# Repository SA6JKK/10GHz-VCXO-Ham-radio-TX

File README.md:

# 10GHz-VCXO-Ham-radio-TX
 A 10 GHz VCXO based FSK transmitter for ham radio

Goal: 0dBm to antenna. 

Goal: Output frequency between 10367-10369 MHz.  

Goal 75x120 mm PCB that fits HAMMOND 1455J1201RD 

https://se.farnell.com/hammond/1455j1201rd/pcb-box-enclosure-alum-red/dp/2469294

VCXO control from external BNC connector. FSK-CW or FSK modes. 

Aisler four layer "HD PCB" stackup for somewhat close to 50 ohms with cheap FR4 substrate. 

# Project Status: 

Schematic: Finished 

Layout: Finished and ordered

Verification: Not fully working :(

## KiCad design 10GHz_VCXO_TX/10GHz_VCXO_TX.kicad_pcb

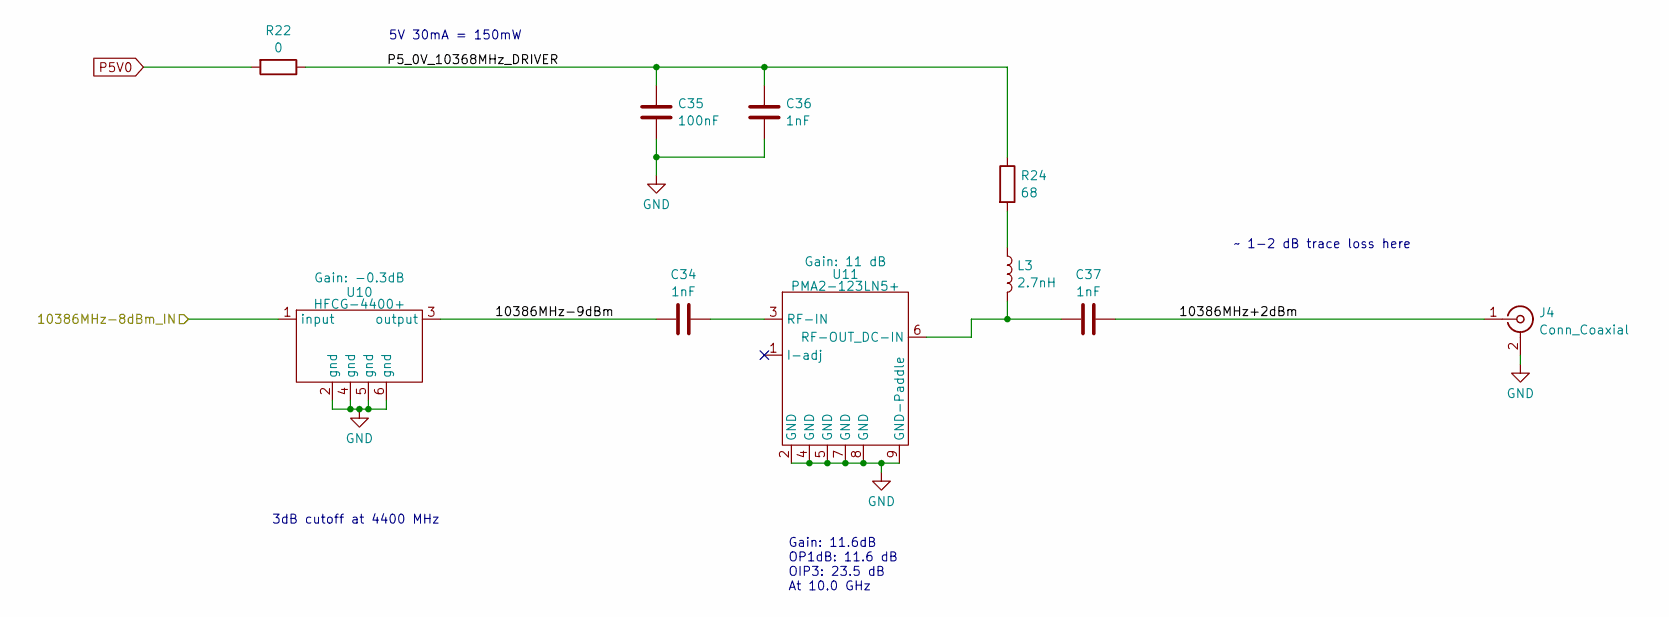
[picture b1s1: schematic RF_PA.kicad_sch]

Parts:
C34, C36, C37: 1nF; C_0402_1005Metric_Pad0.74x0.62mm_HandSolder
C35: 100nF; C_0603_1608Metric_Pad1.08x0.95mm_HandSolder
J4: Conn_Coaxial; SMA_Amphenol_901-143_Horizontal
L3: 2.7nH; L_0603_1608Metric_Pad1.05x0.95mm_HandSolder
R22: 0; R_0603_1608Metric_Pad0.98x0.95mm_HandSolder
R24: 68; R_2512_6332Metric_Pad1.40x3.35mm_HandSolder
U10: HFCG-4400+; Broadcom_DFN-6_2x2mm_P0.65mm
U11: PMA2-123LN5+; DFN-8-1EP_2x2mm_P0.5mm_EP0.6x1.2mm

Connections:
/3x_RF_Multiplier/10368MHz-8dBm_OUT: U10.1 (input); also elsewhere on the board
/RF_PA/10386MHz+2dBm: C37.1, J4.1 (In)
/RF_PA/10386MHz-9dBm: C34.1, U10.3 (output)
/RF_PA/P5_0V_10368MHz_DRIVER: C35.2, C36.2, R22.1, R24.1
GND: C35.1, C36.1, J4.2 (Ext), U10.2 (gnd), U10.4 (gnd), U10.5 (gnd), U10.6 (gnd), U11.2 (GND), U11.4 (GND), U11.5 (GND), U11.7 (GND), U11.8 (GND), U11.9 (GND-Paddle); also elsewhere on the board
unnamed: L3.1, R24.2
unnamed: C34.2, U11.3 (RF-IN)
unnamed: C37.2, L3.2, U11.6 (RF-OUT_DC-IN)
P5V0: R22.2; also elsewhere on the board

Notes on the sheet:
3dB cutoff at 4400 MHz
~ 1-2 dB trace loss here
5V 30mA = 150mW
Gain: 11.6dB OP1dB: 11.6 dB OIP3: 23.5 dB At 10.0 GHz

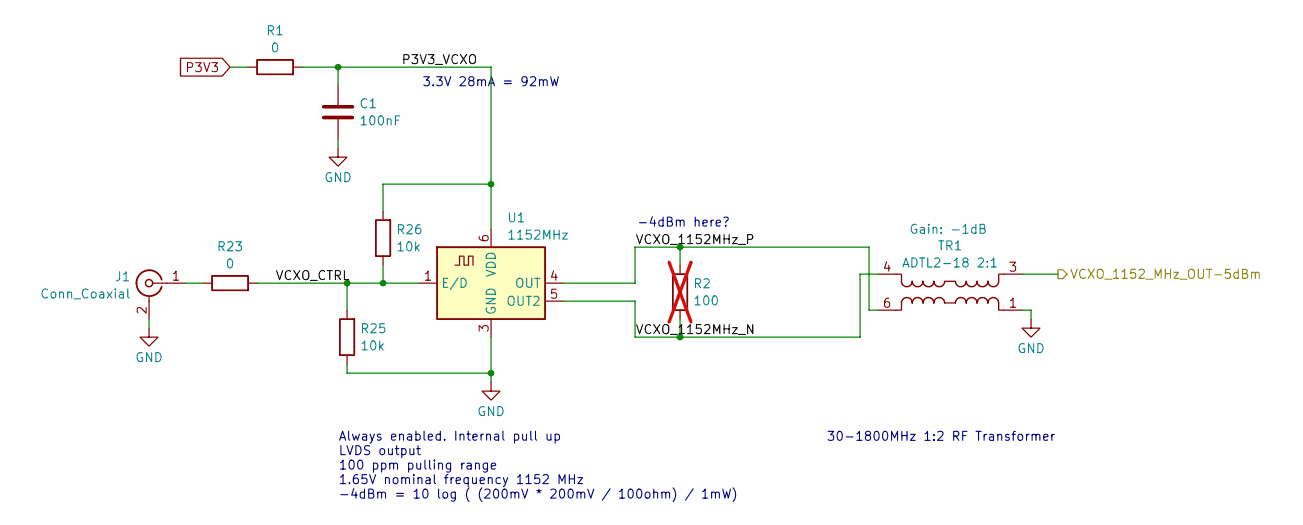
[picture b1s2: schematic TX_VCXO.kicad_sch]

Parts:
C1: 100nF; C_0603_1608Metric_Pad1.08x0.95mm_HandSolder
J1: Conn_Coaxial; BNC_Amphenol_B6252HB-NPP3G-50_Horizontal
R1, R23: 0; R_0603_1608Metric_Pad0.98x0.95mm_HandSolder
R2: 100; R_0603_1608Metric_Pad0.98x0.95mm_HandSolder; not fitted
R25, R26: 10k; R_0603_1608Metric_Pad0.98x0.95mm_HandSolder
TR1: ADTL2-18 2:1; Mini-Circuits_CD542_H2.84mm
U1: 1152MHz; Oscillator_SMD_IDT_JU6-6_7.0x5.0mm_P2.54mm

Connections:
/TX_VCXO/P3V3_VCXO: C1.1, R1.2, R26.2, U1.6 (VDD)
/TX_VCXO/VCXO_1152MHz_N: R2.2, TR1.4, U1.5 (OUT2)
/TX_VCXO/VCXO_1152MHz_P: R2.1, TR1.6, U1.4 (OUT)
/TX_VCXO/VCXO_1152_MHz_OUT-5dBm: TR1.3; also elsewhere on the board
/TX_VCXO/VCXO_CTRL: R23.2, R25.2, R26.1, U1.1 (E/D)
GND: C1.2, J1.2 (Ext), R25.1, TR1.1, U1.3 (GND); also elsewhere on the board
unnamed: J1.1 (In), R23.1
P3V3: R1.1; also elsewhere on the board

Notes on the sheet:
Always enabled. Internal pull up LVDS output 100 ppm pulling range 1.65V nominal frequency 1152 MHz -4dBm = 10 log ( (200mV * 200mV / 100ohm) / 1mW)
-4dBm here?
3.3V 28mA = 92mW
30-1800MHz 1:2 RF Transformer

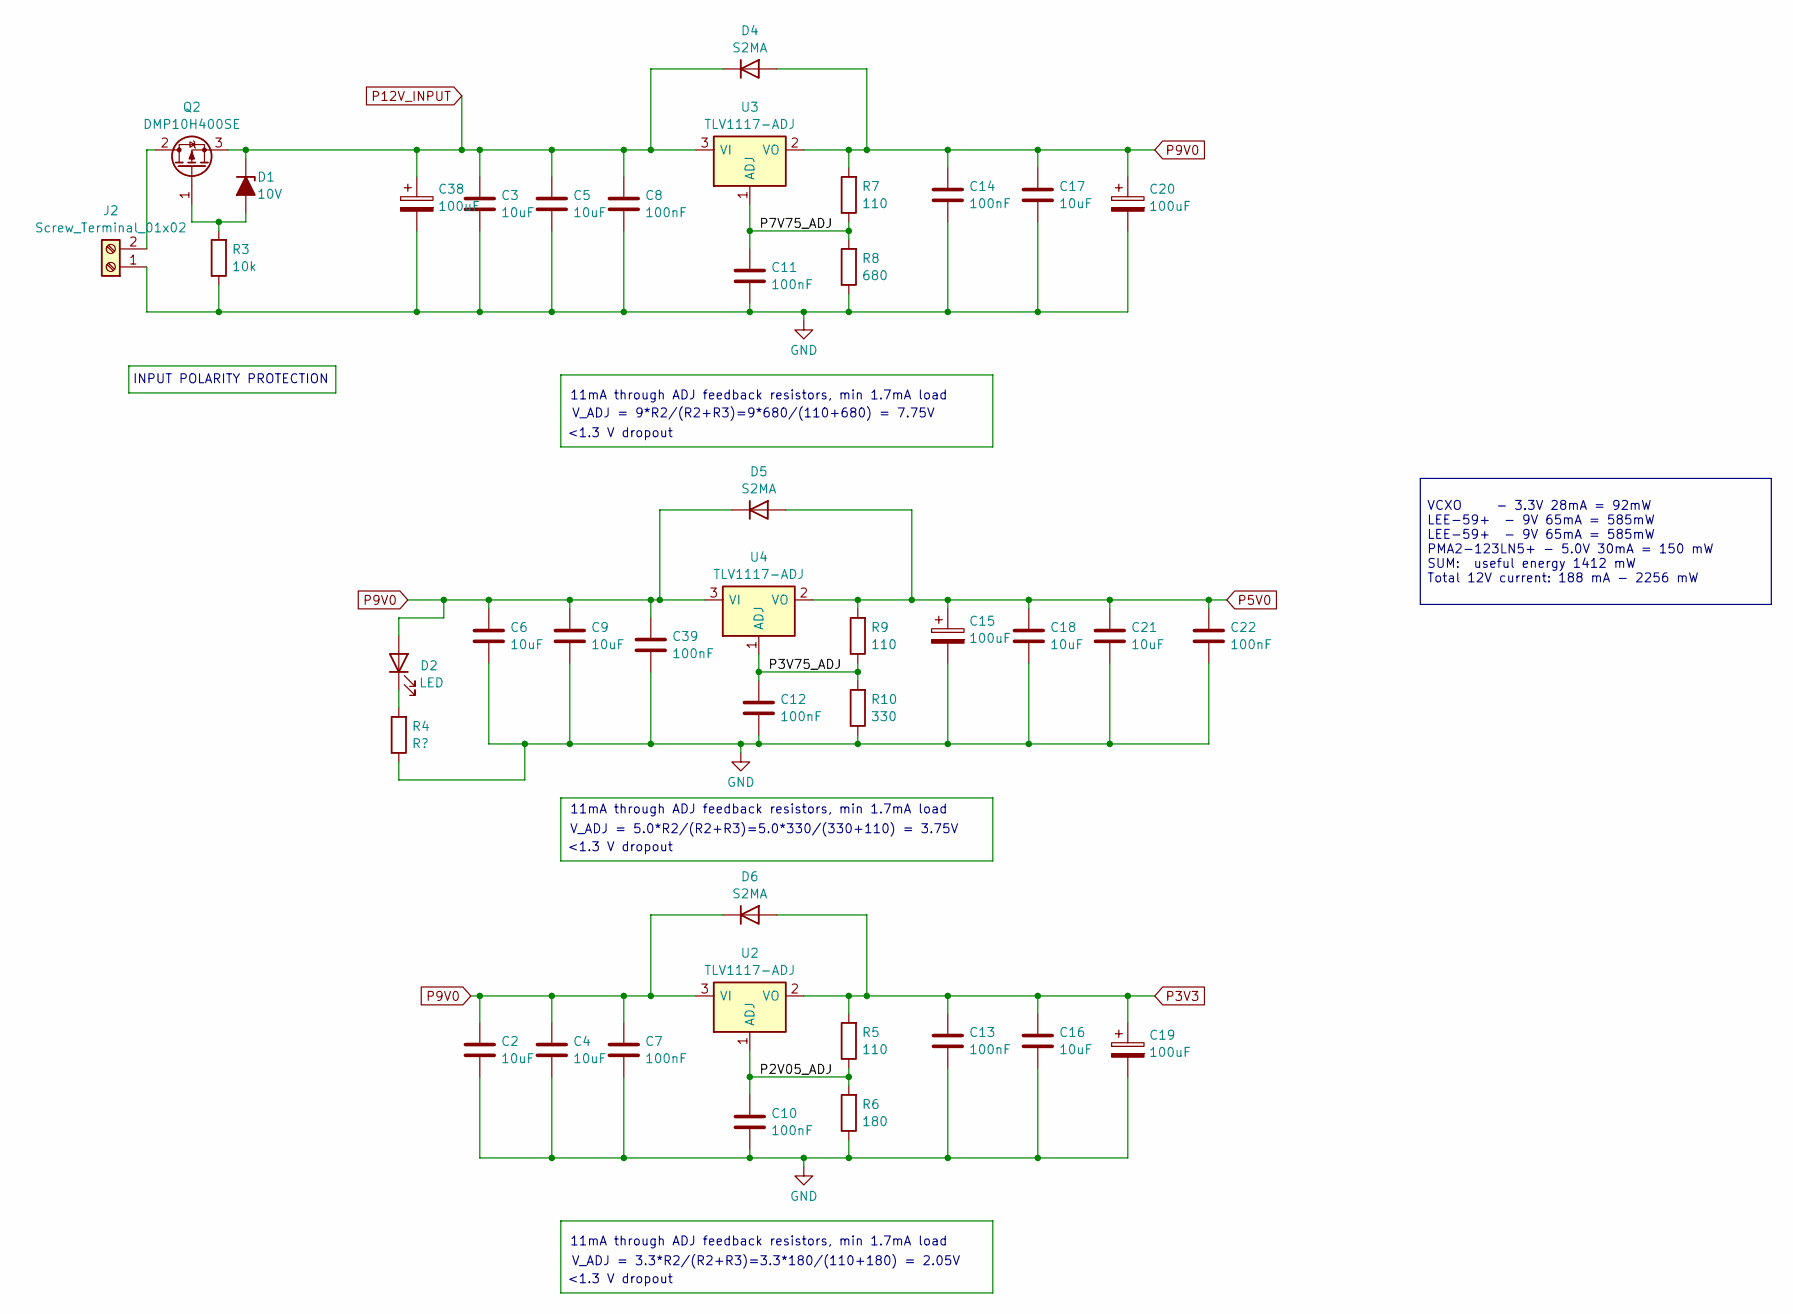
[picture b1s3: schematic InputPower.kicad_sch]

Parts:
C2, C3, C4, C5, C6, C9, C16, C17, C18, C21: 10uF; C_0805_2012Metric_Pad1.18x1.45mm_HandSolder
C7, C8, C10, C11, C12, C13, C14, C22, C39: 100nF; C_0603_1608Metric_Pad1.08x0.95mm_HandSolder
C15, C19, C20, C38: 100uF; CP_Elec_6.3x7.7
D1: 10V; D_SMA
D2: LED; LED_D3.0mm_Horizontal_O6.35mm_Z10.0mm
D4, D5, D6: S2MA; D_SMA
J2: Screw_Terminal_01x02; Altech_AK100_1x02_P5.00mm
Q2: DMP10H400SE; SOT-223-3_TabPin2
R3: 10k; R_0603_1608Metric_Pad0.98x0.95mm_HandSolder
R4: R?; R_0603_1608Metric_Pad0.98x0.95mm_HandSolder
R5, R7, R9: 110; R_0603_1608Metric_Pad0.98x0.95mm_HandSolder
R6: 180; R_0603_1608Metric_Pad0.98x0.95mm_HandSolder
R8: 680; R_0603_1608Metric_Pad0.98x0.95mm_HandSolder
R10: 330; R_0603_1608Metric_Pad0.98x0.95mm_HandSolder
U2, U3, U4: TLV1117-ADJ; SOT-223-3_TabPin2

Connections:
/InputPower/P2V05_ADJ: C10.2, R5.1, R6.2, U2.1 (ADJ)
/InputPower/P3V75_ADJ: C12.2, R9.1, R10.2, U4.1 (ADJ)
/InputPower/P7V75_ADJ: C11.2, R7.1, R8.2, U3.1 (ADJ)
GND: C2.1, C3.1, C4.1, C5.1, C6.1, C7.1, C8.1, C9.1, C10.1, C11.1, C12.1, C13.2, C14.1, C15.2, C16.2, C17.1, C18.1, C19.2, C20.2, C21.1, C22.1, C38.2, C39.1, J2.1, R3.1, R4.1, R6.1, R8.1, R10.1; also elsewhere on the board
unnamed: D1.2 (A), Q2.1 (G), R3.2
unnamed: D2.1 (K), R4.2
unnamed: J2.2, Q2.2 (D)
P3V3: C13.1, C16.1, C19.1, D6.2 (A), R5.2, U2.2 (VO); also elsewhere on the board
P5V0: C15.1, C18.2, C21.2, C22.2, D5.2 (A), R9.2, U4.2 (VO); also elsewhere on the board
P9V0: C2.2, C4.2, C6.2, C7.2, C9.2, C14.2, C17.2, C20.1, C39.2, D2.2 (A), D4.2 (A), D5.1 (K), D6.1 (K), R7.2, U2.3 (VI), U3.2 (VO), U4.3 (VI); also elsewhere on the board
P12V_INPUT: C3.2, C5.2, C8.2, C38.1, D1.1 (K), D4.1 (K), Q2.3 (S), U3.3 (VI)

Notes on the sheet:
<1.3 V dropout
11mA through ADJ feedback resistors, min 1.7mA load
V_ADJ = 9*R2/(R2+R3)=9*680/(110+680) = 7.75V
VCXO - 3.3V 28mA = 92mW LEE-59+ - 9V 65mA = 585mW LEE-59+ - 9V 65mA = 585mW PMA2-123LN5+ - 5.0V 30mA = 150 mW SUM: useful energy 1412 mW Total 12V current: 188 mA - 2256 mW
INPUT POLARITY PROTECTION
V_ADJ = 5.0*R2/(R2+R3)=5.0*330/(330+110) = 3.75V
V_ADJ = 3.3*R2/(R2+R3)=3.3*180/(110+180) = 2.05V

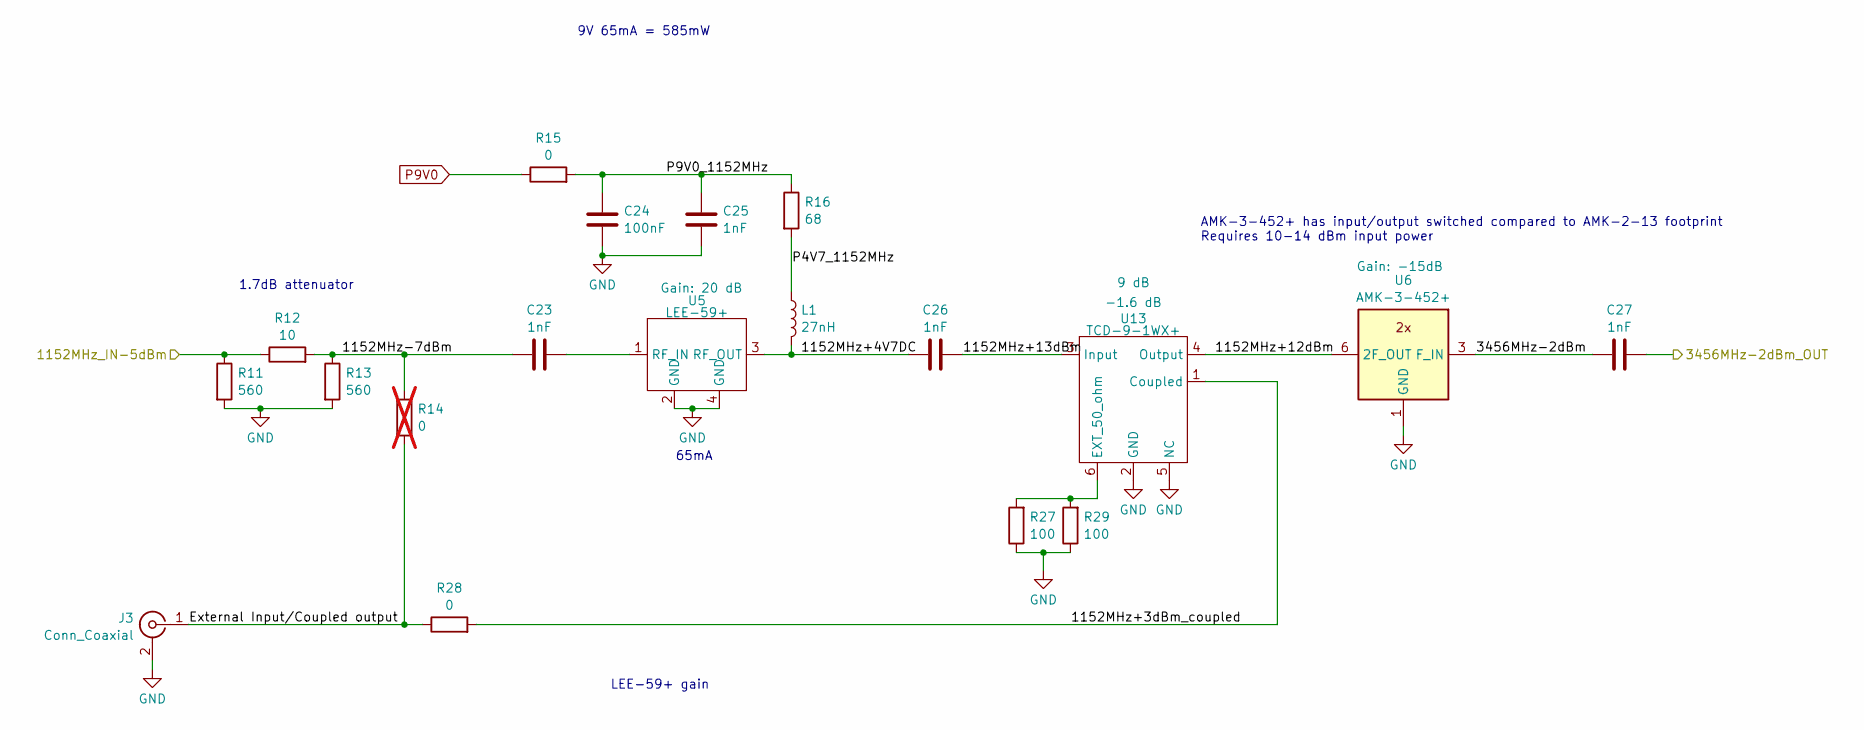
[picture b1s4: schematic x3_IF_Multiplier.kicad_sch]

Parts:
C23, C25, C26, C27: 1nF; C_0402_1005Metric_Pad0.74x0.62mm_HandSolder
C24: 100nF; C_0603_1608Metric_Pad1.08x0.95mm_HandSolder
J3: Conn_Coaxial; SMA_Amphenol_901-143_Horizontal
L1: 27nH; L_0603_1608Metric_Pad1.05x0.95mm_HandSolder
R11, R13: 560; R_0603_1608Metric_Pad0.98x0.95mm_HandSolder
R12: 10; R_0603_1608Metric_Pad0.98x0.95mm_HandSolder
R14: 0; R_0603_1608Metric_Pad0.98x0.95mm_HandSolder; not fitted
R15, R28: 0; R_0603_1608Metric_Pad0.98x0.95mm_HandSolder
R16: 68; R_2512_6332Metric_Pad1.40x3.35mm_HandSolder
R27, R29: 100; R_0603_1608Metric_Pad0.98x0.95mm_HandSolder
U5: LEE-59+; Mini-Circuits_FG873-4_3x3mm
U6: AMK-3-452+; Mini-Circuits_CD542_LandPatternPL-052
U13: TCD-9-1WX+; Mini-Circuits_DB1627

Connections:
/3x_RF_Multiplier/3456MHz-2dBm_IN: C27.2; also elsewhere on the board
/TX_VCXO/VCXO_1152_MHz_OUT-5dBm: R11.1, R12.1; also elsewhere on the board
/x3_IF_Multiplier/1152MHz+3dBm_coupled: R28.2, U13.1 (Coupled)
/x3_IF_Multiplier/1152MHz+4V7DC: C26.1, L1.2, U5.3 (RF_OUT)
/x3_IF_Multiplier/1152MHz+12dBm: U6.6 (2F_OUT), U13.4 (Output)
/x3_IF_Multiplier/1152MHz+13dBm: C26.2, U13.3 (Input)
/x3_IF_Multiplier/1152MHz-7dBm: C23.1, R12.2, R13.1, R14.1
/x3_IF_Multiplier/3456MHz-2dBm: C27.1, U6.3 (F_IN)
/x3_IF_Multiplier/External Input/Coupled output: J3.1 (In), R14.2, R28.1
/x3_IF_Multiplier/P4V7_1152MHz: L1.1, R16.2
/x3_IF_Multiplier/P9V0_1152MHz: C24.2, C25.2, R15.2, R16.1
GND: C24.1, C25.1, J3.2 (Ext), R11.2, R13.2, R27.1, R29.1, U5.2 (GND), U5.4 (GND), U6.1 (GND), U6.4 (GND), U6.5 (GND), U13.2 (GND), U13.5 (NC); also elsewhere on the board
unnamed: C23.2, U5.1 (RF_IN)
unnamed: R27.2, R29.2, U13.6 (EXT_50_ohm)
P9V0: R15.1; also elsewhere on the board

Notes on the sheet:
AMK-3-452+ has input/output switched compared to AMK-2-13 footprint Requires 10-14 dBm input power
9V 65mA = 585mW
1.7dB attenuator
LEE-59+ gain
65mA

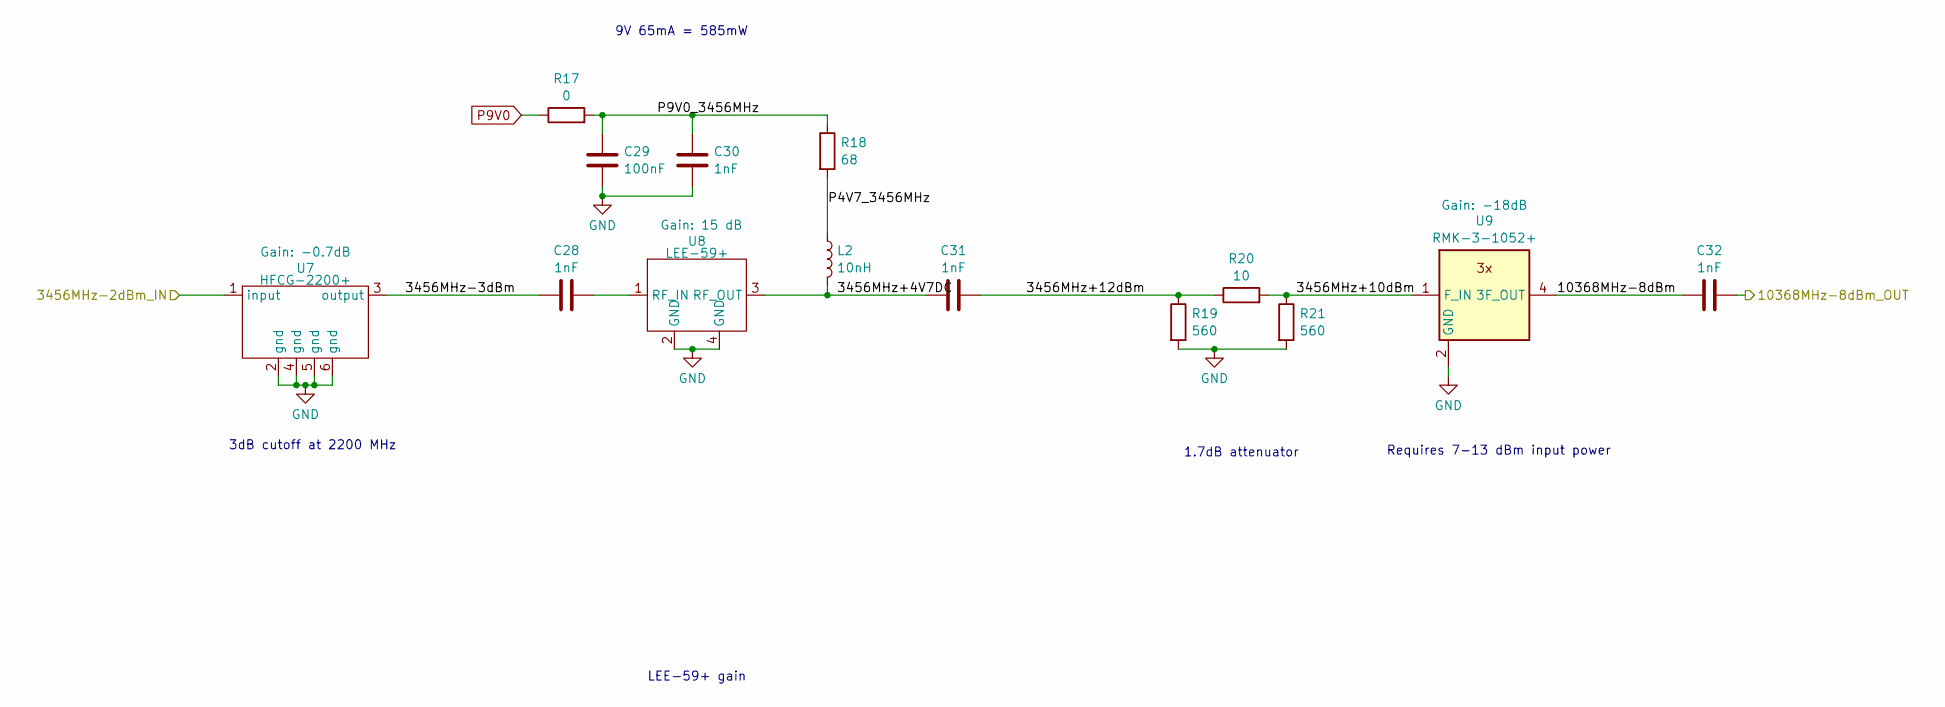
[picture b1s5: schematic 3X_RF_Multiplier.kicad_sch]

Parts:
C28, C30, C31, C32: 1nF; C_0402_1005Metric_Pad0.74x0.62mm_HandSolder
C29: 100nF; C_0603_1608Metric_Pad1.08x0.95mm_HandSolder
L2: 10nH; L_0603_1608Metric_Pad1.05x0.95mm_HandSolder
R17: 0; R_0603_1608Metric_Pad0.98x0.95mm_HandSolder
R18: 68; R_2512_6332Metric_Pad1.40x3.35mm_HandSolder
R19, R21: 560; R_0603_1608Metric_Pad0.98x0.95mm_HandSolder
R20: 10; R_0603_1608Metric_Pad0.98x0.95mm_HandSolder
U7: HFCG-2200+; Broadcom_DFN-6_2x2mm_P0.65mm
U8: LEE-59+; Mini-Circuits_FG873-4_3x3mm
U9: RMK-3-1052+; Mini-Circuits_TT1224_LandPatternPL-258_ClockwisePinNumbering

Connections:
/3x_RF_Multiplier/3456MHz+4V7DC: C31.2, L2.2, U8.3 (RF_OUT)
/3x_RF_Multiplier/3456MHz+10dBm: R20.2, R21.1, U9.1 (F_IN)
/3x_RF_Multiplier/3456MHz+12dBm: C31.1, R19.1, R20.1
/3x_RF_Multiplier/3456MHz-2dBm_IN: U7.1 (input); also elsewhere on the board
/3x_RF_Multiplier/3456MHz-3dBm: C28.1, U7.3 (output)
/3x_RF_Multiplier/10368MHz-8dBm: C32.1, U9.4 (3F_OUT)
/3x_RF_Multiplier/10368MHz-8dBm_OUT: C32.2; also elsewhere on the board
/3x_RF_Multiplier/P4V7_3456MHz: L2.1, R18.2
/3x_RF_Multiplier/P9V0_3456MHz: C29.2, C30.2, R17.2, R18.1
GND: C29.1, C30.1, R19.2, R21.2, U7.2 (gnd), U7.4 (gnd), U7.5 (gnd), U7.6 (gnd), U8.2 (GND), U8.4 (GND), U9.2 (GND), U9.3 (GND), U9.5 (GND), U9.6 (GND); also elsewhere on the board
unnamed: C28.2, U8.1 (RF_IN)
P9V0: R17.1; also elsewhere on the board

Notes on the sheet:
1.7dB attenuator
Requires 7-13 dBm input power
9V 65mA = 585mW
LEE-59+ gain
3dB cutoff at 2200 MHz

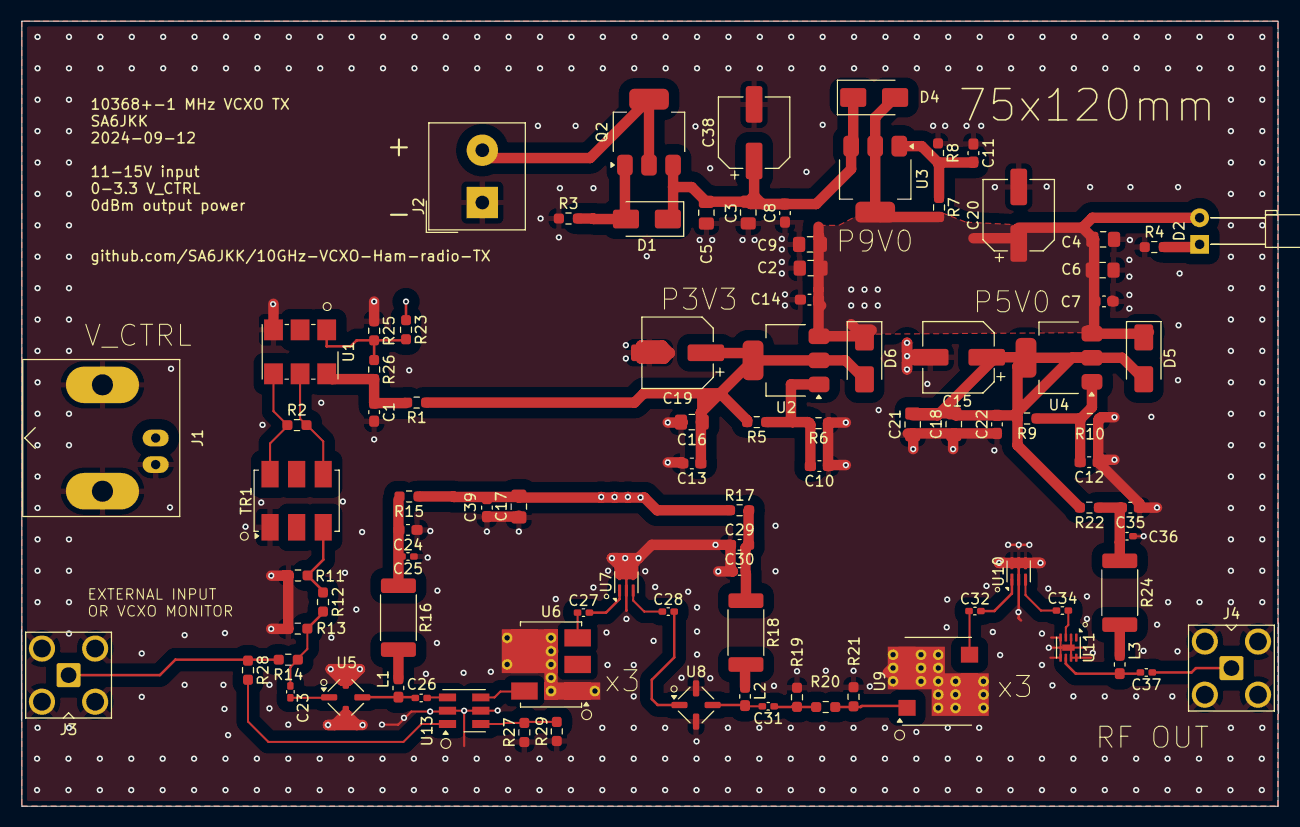
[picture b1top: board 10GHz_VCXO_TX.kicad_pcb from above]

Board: 4 copper layers, 120.0 x 75.0 mm, 93 parts (0 on the bottom side), 44 nets.

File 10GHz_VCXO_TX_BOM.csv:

"Reference","Value","Datasheet","Footprint","Qty","DNP"
"C1,C7,C8,C10,C11,C12,C13,C14,C22,C24,C29,C35,C39","100nF","~","Capacitor_SMD:C_0603_1608Metric_Pad1.08x0.95mm_HandSolder","13",""
"C2,C3,C4,C5,C6,C9,C16,C17,C18,C21","10uF","~","Capacitor_SMD:C_0805_2012Metric_Pad1.18x1.45mm_HandSolder","10",""
"C15,C19,C20,C38","100uF","~","Capacitor_SMD:CP_Elec_6.3x7.7","4",""
"C23,C25,C26,C27,C28,C30,C31,C32,C34,C36,C37","1nF","~","Capacitor_SMD:C_0402_1005Metric_Pad0.74x0.62mm_HandSolder","11",""
"D1","10V","~","Diode_SMD:D_SMA","1",""
"D2","LED ","~","LED_THT:LED_D3.0mm_Horizontal_O6.35mm_Z10.0mm","1",""
"D4,D5,D6","S2MA","https://www.farnell.com/datasheets/2863973.pdf","Diode_SMD:D_SMA","3",""
"J1,J3,J4","Conn_Coaxial"," ~","-- mixed values --","3",""
"J2","Screw_Terminal_01x02","~","TerminalBlock_Altech:Altech_AK100_1x02_P5.00mm","1",""
"L1","27nH","~","Inductor_SMD:L_0603_1608Metric_Pad1.05x0.95mm_HandSolder","1",""
"L2","10nH","~","Inductor_SMD:L_0603_1608Metric_Pad1.05x0.95mm_HandSolder","1",""
"L3","2.7nH","~","Inductor_SMD:L_0603_1608Metric_Pad1.05x0.95mm_HandSolder","1",""
"Q2","DMP10H400SE","https://www.farnell.com/datasheets/2814417.pdf","Package_TO_SOT_SMD:SOT-223-3_TabPin2","1",""
"R1,R15,R17,R22,R23","0","~","Resistor_SMD:R_0603_1608Metric_Pad0.98x0.95mm_HandSolder","5",""
"R2","100","~","Resistor_SMD:R_0603_1608Metric_Pad0.98x0.95mm_HandSolder","1","DNP"
"R3,R25,R26","10k","~","Resistor_SMD:R_0603_1608Metric_Pad0.98x0.95mm_HandSolder","3",""
"R4","R?","~","Resistor_SMD:R_0603_1608Metric_Pad0.98x0.95mm_HandSolder","1",""
"R5,R7,R9","110","~","Resistor_SMD:R_0603_1608Metric_Pad0.98x0.95mm_HandSolder","3",""
"R6","180","~","Resistor_SMD:R_0603_1608Metric_Pad0.98x0.95mm_HandSolder","1",""
"R8","680","~","Resistor_SMD:R_0603_1608Metric_Pad0.98x0.95mm_HandSolder","1",""
"R10","330","~","Resistor_SMD:R_0603_1608Metric_Pad0.98x0.95mm_HandSolder","1",""
"R11,R13,R19,R21","560","~","Resistor_SMD:R_0603_1608Metric_Pad0.98x0.95mm_HandSolder","4",""
"R12,R20","10","~","Resistor_SMD:R_0603_1608Metric_Pad0.98x0.95mm_HandSolder","2",""
"R14","0","~","Resistor_SMD:R_0603_1608Metric_Pad0.98x0.95mm_HandSolder","1","DNP"
"R16,R18,R24","68","~","Resistor_SMD:R_2512_6332Metric_Pad1.40x3.35mm_HandSolder","3",""
"TR1","ADTL2-18 2:1 ","https://www.minicircuits.com/pdfs/ADTL2-18+.pdf","RF_Mini-Circuits:Mini-Circuits_CD542_H2.84mm","1",""
"U1","1152MHz","https://www.renesas.com/us/en/document/dst/xu-family-low-pha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","Oscillator:Oscillator_SMD_IDT_JU6-6_7.0x5.0mm_P2.54mm","1",""
"U2,U3,U4","TLV1117-ADJ","http://www.ti.com/lit/ds/symlink/tlv1117.pdf","Package_TO_SOT_SMD:SOT-223-3_TabPin2","3",""
"U5,U8","LEE-59+","https://www.mouser.se/datasheet/2/1030/LEE_59_2b-1700827.pdf","Package_DFN_QFN:Mini-Circuits_FG873-4_3x3mm","2",""
"U6","AMK-3-452+","https://www.mouser.se/datasheet/2/1030/AMK_3_452_2b-2936698.pdf","RF_Mini-Circuits:Mini-Circuits_CD542_LandPatternPL-052","1",""
"U7","HFCG-2200+","https://www.mouser.se/datasheet/2/1030/HFCG_2200_2b-3077494.pdf","OptoDevice:Broadcom_DFN-6_2x2mm_P0.65mm","1",""
"U9","RMK-3-1052+","https://www.mouser.se/datasheet/2/1030/RMK_3_1052_2b-3305585.pdf","RF_Mini-Circuits:Mini-Circuits_TT1224_LandPatternPL-258_ClockwisePinNumbering","1",""
"U10","HFCG-4400+","https://www.mouser.se/datasheet/2/1030/HFCG_4400_2b-2256271.pdf","OptoDevice:Broadcom_DFN-6_2x2mm_P0.65mm","1",""
"U11","PMA2-123LN5+","https://www.mouser.se/datasheet/2/1030/PMA2_123LN5_2b-1701048.pdf","Package_DFN_QFN:DFN-8-1EP_2x2mm_P0.5mm_EP0.6x1.2mm","1",""

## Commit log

2024-06-20 Start project!
    LDO + VCXO
2024-06-20 update gitignore
    hope this works...
2024-06-21 Add multipliers
2024-06-23 Update Hierarchy + LEE-59+
2024-06-23 add LEE-59+ footprint
2024-06-24 Update README.md with enclosure
2024-06-24 Update board outline, floorplan and tidy up
2024-06-24 Add BOM cost analysis
2024-06-26 Add HP filters after multiplier
2024-06-30 Add PMA2-123LN5+
2024-07-05 Add PA HMC952A & LED
2024-07-06 Add optional external oscillator input
2024-07-07 Add 5V Linear Regulator
2024-07-07 Fixed power consumption calculation
2024-07-23 Add more decoupling & tidying of schematic
2024-07-28 Update README.md with 0dBm goal
2024-07-28 Finished schematic, update BOM cost analysis
    ~1000 kr components.
2024-07-28 Update README.md again FSK modes clarification
2024-07-28 Finalize placing, initial routing, schematic tidying
2024-07-28 Initial routing complete
2024-07-29 Added more documentation to schematic
2024-07-30 Update inductor component values schematic
2024-08-07 10uF 0603 -> 10uF 0805
2024-08-08 Add schematic pdf and layout assembly pdf
2024-08-08 Update README.md with project status
2024-08-14 Add layout copper fill
    and update origin, bigger electrolytics
2024-08-19 Add via stitching and remove edge solder mask
2024-08-19 Add first render
2024-08-19 Update README.md with render
2024-08-19 Add silk screen text to connectors
2024-08-21 Update README.md with stackup
2024-08-23 Update BOM with ordering status
2024-08-23 Add github link text
2024-08-24 Removed solder mask over 10 GHz traces
2024-08-29 Remove more solder mask
2024-08-29 Update render
2024-08-29 Update README.md with v2 render
2024-08-30 Prepare for TCD-9-1WX+ addition
    To enable buffered VCXO output for frequency counter
2024-08-30 Add TCD-9-1WX+ coupler for frequency measurements
2024-09-08 Add 9 dB coupler for VCXO monitor to layout
2024-09-09 Tidying up layout and new render
2024-09-09 Update README.md new render
2024-09-10 Update plots
2024-09-10 Add more GND vias
2024-09-12 Final touches before ordering
2024-09-12 Updated date of board
2024-09-12 Update README.md, layout ordered
2024-09-12 Add render v4
2024-09-12 Update README.md with render v4
2024-09-14 Update README.md -CW
2024-09-14 Update plots folder
2024-09-28 Add interactive BOM for assembly
2024-09-28 Add first test report and assembled image
2024-09-28 Update README.md with verification status and new image
2024-10-19 Update test report with U11 bypassed results
2024-10-26 Update 1152 MHz attenuator
2024-12-03 Create RF-calculations for 10 GHz lineup
2025-02-25 Updating TODO in schematic
2025-02-25 Update RF-calculations again
2025-02-25 Removed typo
